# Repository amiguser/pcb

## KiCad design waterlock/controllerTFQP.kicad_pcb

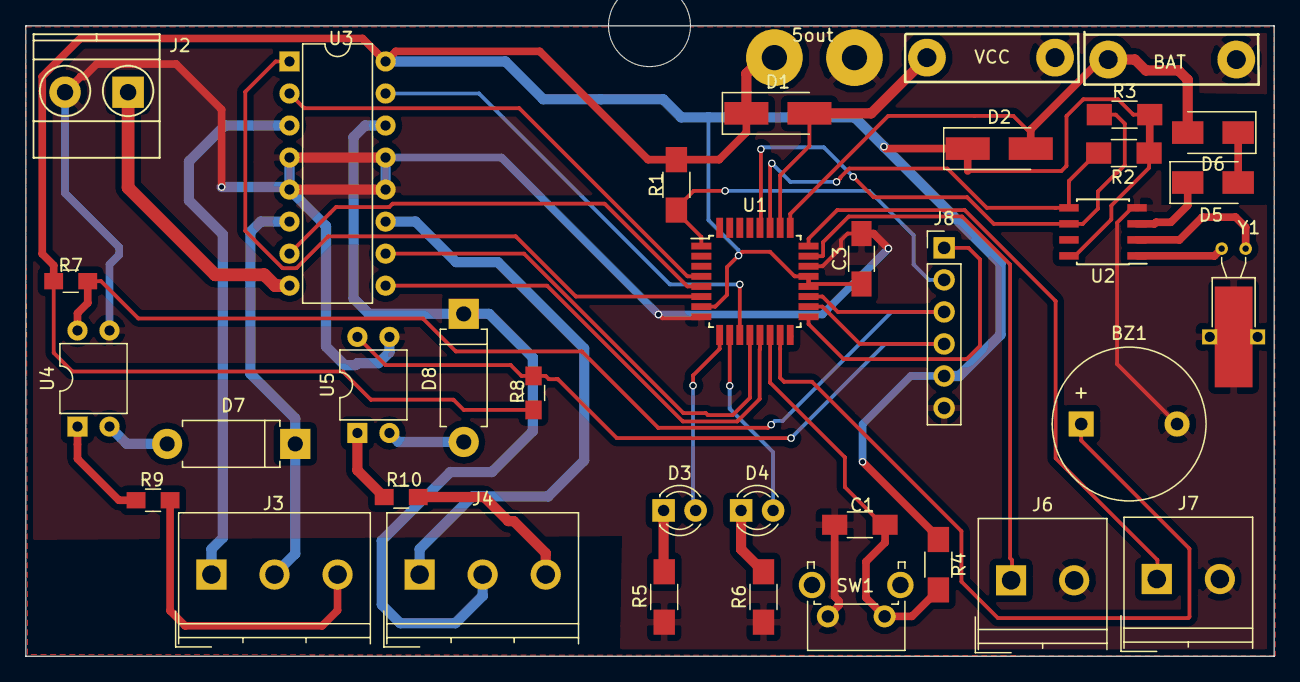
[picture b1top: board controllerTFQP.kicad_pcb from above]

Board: 2 copper layers, 99.0 x 50.0 mm, 37 parts (0 on the bottom side), 39 nets.

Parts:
5out: SolderWirePad_2x_2mmDrill
BAT: Battery; WireConnection_1.50mmDrill
BZ1: Buzzer; Buzzer_12x9.5RM7.6
C1, C3: 10m; C_1206_HandSoldering
D1: SS16; D_SMA_Handsoldering
D2: 1N; D_SMA_Handsoldering
D3: LowBatt; LED_D3.0mm
D4: Flooding; LED_D3.0mm
D5, D6: D_ALT; D_SMA
D7, D8: 1N5822; D_DO-15_P10.16mm_Horizontal
J2: v12; TerminalBlock_Pheonix_MKDS1.5-2pol
J3, J4: 300-031-7,5; TerminalBlock_Philmore_TB133_03x5mm_Straight
J6, J7: 301-021-12; TerminalBlock_Philmore_TB132_02x5mm_Straight
J8: Conn_01x06; Pin_Header_Straight_1x06_Pitch2.54mm
R1, R2, R3, R4, R5, R6: 10k; R_1206_HandSoldering
R7, R8: 10k; R_0805_HandSoldering
R9, R10: 1k; R_0805_HandSoldering
SW1: Tactile Angle; SW_Tactile_SPST_Angled_PTS645Vx39-2LFS
U1: ATMEGA8-16PU; TQFP-32_7x7mm_Pitch0.8mm
U2: DS1307+; SOIC-8_3.9x4.9mm_Pitch1.27mm
U3: L293D; DIP-16_W7.62mm
U4, U5: PC817; DIP-4_W7.62mm
VCC: v5; WireConnection_1.50mmDrill
Y1: 32768Hz; Crystal_C38-LF_d3.0mm_l8.0mm_Horizontal_1EP_style2

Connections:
+5V: 5out.1, C3.1, D1.1, D2.1, J8.5, R1.1, R2.2, R3.2, R4.1, R7.2, R8.2, U1.7, U1.20, U1.21, U2.8, U3.16
/Line1: J6.1, U1.23
/Line2: J7.1, U1.24
/MISO: J8.4, R8.1, U1.18, U5.4
/MOSI: J8.1, U1.17
/MotorsShield/m1black: D7.1, J3.2, U3.6
/MotorsShield/m1sensor: J3.3, R9.1
/MotorsShield/m2black: D8.1, J4.2, U3.14
/MotorsShield/m2sensor: J4.3, R10.1
/RESET: J8.2, R1.2, U1.1
/SCK: J8.3, R7.1, U1.19, U4.4
/SCL: R3.1, U1.28, U2.6
/SDA: R2.1, U1.27, U2.5
/btn_1: C1.2, R4.2, SW1.1, U1.14
/buzz: BZ1.1, U1.15
/en12: U1.6, U3.1
/en34: U1.13, U3.9
/led1: D3.2, U1.9
/led2: D4.2, U1.10
/m1a: U1.4, U3.2
/m2a: U1.5, U3.7
/m3a: U1.12, U3.10
/m4a: U1.11, U3.15
/pwr_c1: BAT.1, D2.2, D6.2, U1.25
/pwr_c2: D1.2, U1.26, VCC.1
GND: 5out.1, BAT.2, BZ1.2, C1.1, C3.2, J2.2, J6.2, J7.2, J8.6, R5.2, R6.2, SW1.2, U1.8, U1.22, U2.4, U3.4, U3.5, U3.12, U3.13, U4.3, U5.3, VCC.2, Y1.3
unnamed: D3.1, R5.1
unnamed: D4.1, R6.1
unnamed: D5.1, U2.3
unnamed: D5.2, D6.1
unnamed: D7.2, U4.2
unnamed: D8.2, U5.2
unnamed: J2.1, U3.8
unnamed: J3.1, U3.3
unnamed: J4.1, U3.11
unnamed: R9.2, U4.1
unnamed: R10.2, U5.1
unnamed: U2.1, Y1.1
unnamed: U2.2, Y1.2

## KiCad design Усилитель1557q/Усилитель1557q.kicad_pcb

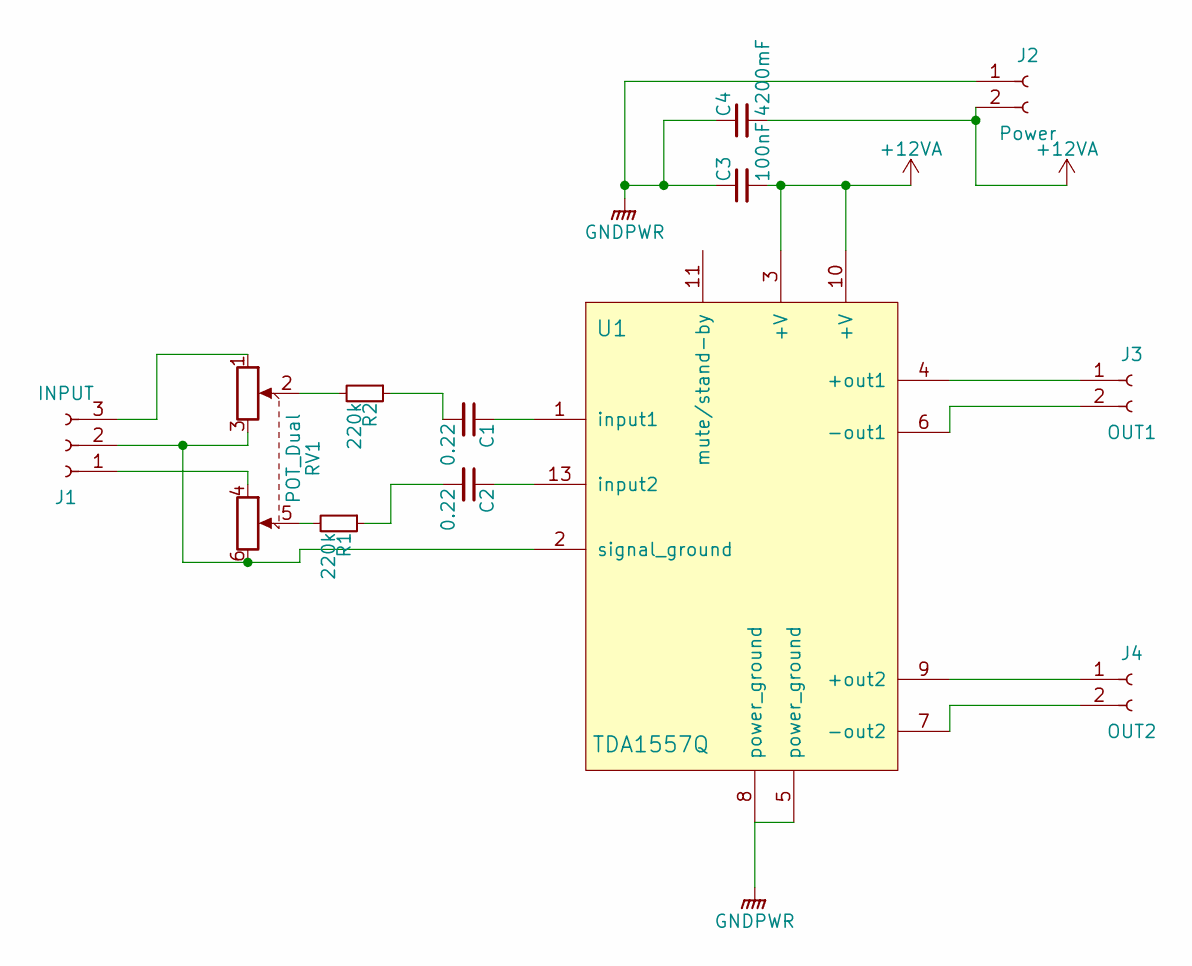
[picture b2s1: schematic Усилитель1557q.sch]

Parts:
C1, C2: 0.22; C_Disc_D11.0mm_W5.0mm_P7.50mm
C3: 100nF; C_Disc_D11.0mm_W5.0mm_P7.50mm
C4: 4200mF; CP_Radial_D13.0mm_P5.00mm
J1: INPUT; TerminalBlock_Pheonix_MKDS1.5-3pol
J2: Power; TerminalBlock_Pheonix_MKDS1.5-2pol
J3: OUT1; TerminalBlock_Pheonix_MKDS1.5-2pol
J4: OUT2; TerminalBlock_Pheonix_MKDS1.5-2pol
R1, R2: 220k; R_Axial_DIN0204_L3.6mm_D1.6mm_P7.62mm_Horizontal
RV1: POT_Dual; Potentiometer_Alps_RK163_Double_Vertical
U1: TDA1557Q; Multiwatt_15_Vertical

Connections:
+12VA: C3.2, C4.2, J2.2, U1.3 (+V), U1.10 (+V)
GNDPWR: C3.1, C4.1, J2.1, U1.5 (power_ground), U1.8 (power_ground)
unnamed: C1.1, U1.1 (input1)
unnamed: C1.2, R2.1
unnamed: C2.1, U1.13 (input2)
unnamed: C2.2, R1.1
unnamed: J1.1, RV1.4
unnamed: J1.2, RV1.3, RV1.6, U1.2 (signal_ground)
unnamed: J1.3, RV1.1
unnamed: J3.1, U1.4 (+out1)
unnamed: J3.2, U1.6 (-out1)
unnamed: J4.1, U1.9 (+out2)
unnamed: J4.2, U1.7 (-out2)
unnamed: R1.2, RV1.5
unnamed: R2.2, RV1.2

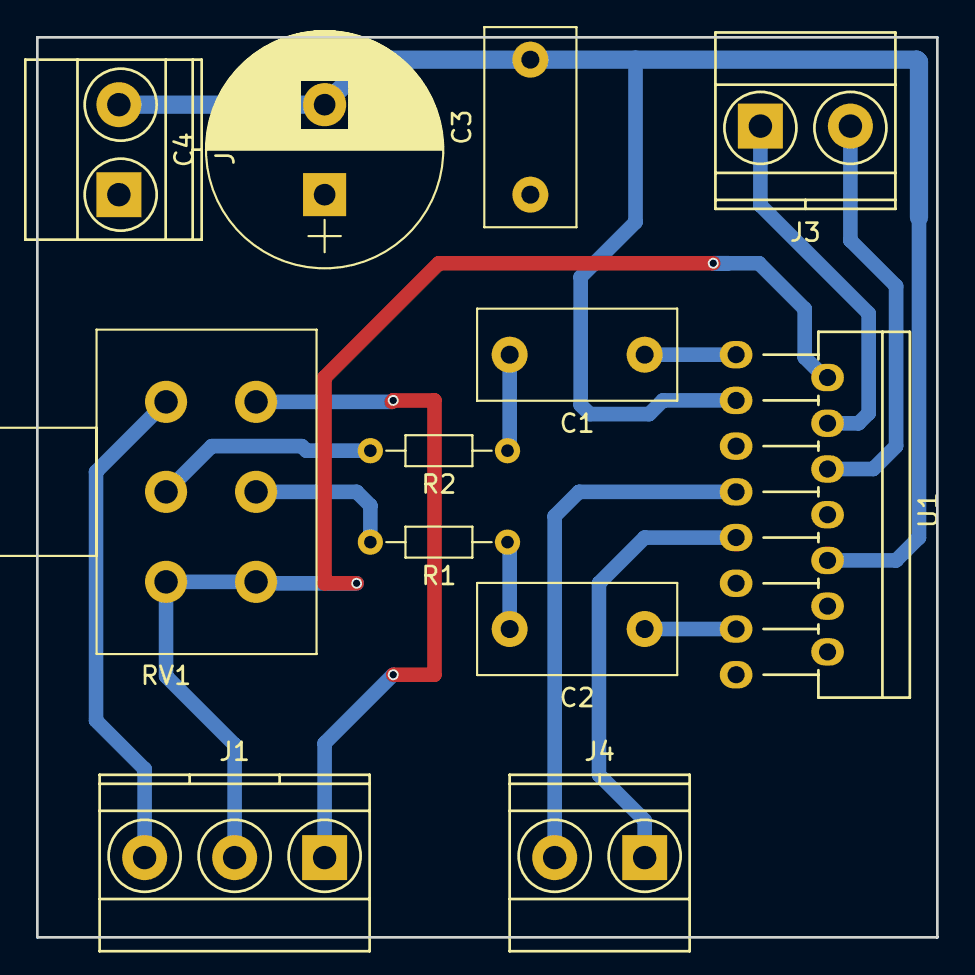
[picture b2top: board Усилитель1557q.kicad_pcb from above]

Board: 2 copper layers, 50.0 x 50.0 mm, 12 parts (0 on the bottom side), 15 nets.

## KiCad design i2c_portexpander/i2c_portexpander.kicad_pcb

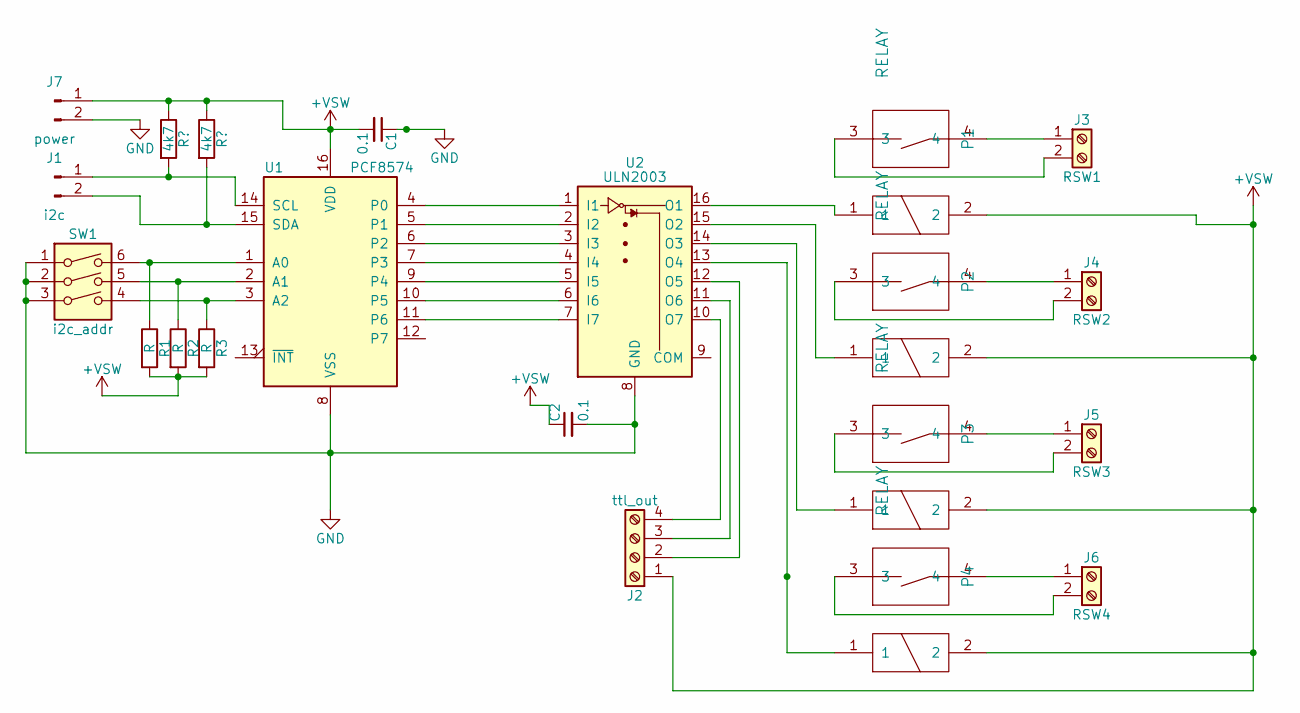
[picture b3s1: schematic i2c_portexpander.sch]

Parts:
C1, C2: 0.1; C_1206_HandSoldering
J1: i2c; Molex_KK-6410-02_02x2.54mm_Straight
J2: ttl_out; WAGO_734_4pin_Straight
J3: RSW1; TerminalBlock_Pheonix_MKDS1.5-2pol
J4: RSW2; TerminalBlock_Pheonix_MKDS1.5-2pol
J5: RSW3; TerminalBlock_Pheonix_MKDS1.5-2pol
J6: RSW4; TerminalBlock_Pheonix_MKDS1.5-2pol
J7: power; Molex_KK-6410-02_02x2.54mm_Straight
P1, P2, P3, P4: RELAY; Relay-841-1A
R1, R2, R3: R; R_0805_HandSoldering
SW1: i2c_addr; SW_DIP_x3_W8.61mm_Slide_LowProfile
U1: PCF8574; SOIC-16W_7.5x10.3mm_Pitch1.27mm
U2: ULN2003; SOIC-16W_5.3x10.2mm_Pitch1.27mm

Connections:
+VSW: C1.2, C2.1, J2.1, J7.1, P1.2, P2.2, P3.2, P4.2, R1.2, R2.2, R3.2, U1.16 (VDD); also elsewhere on the board
GND: C1.1, C2.2, J7.2, SW1.1, SW1.2, SW1.3, U1.8 (VSS), U2.8 (GND)
unnamed 2: J1.1, U1.14 (SCL); also elsewhere on the board
unnamed 3: J1.2, U1.15 (SDA); also elsewhere on the board
unnamed: J2.2, U2.12 (O5)
unnamed: J2.3, U2.11 (O6)
unnamed: J2.4, U2.10 (O7)
unnamed: J3.1, P1.4
unnamed: J3.2, P1.3
unnamed: J4.1, P2.4
unnamed: J4.2, P2.3
unnamed: J5.1, P3.4
unnamed: J5.2, P3.3
unnamed: J6.1, P4.4
unnamed: J6.2, P4.3
unnamed: P1.1, U2.16 (O1)
unnamed: P2.1, U2.15 (O2)
unnamed: P3.1, U2.14 (O3)
unnamed: P4.1, U2.13 (O4)
unnamed: R1.1, SW1.6, U1.1 (A0)
unnamed: R2.1, SW1.5, U1.2 (A1)
unnamed: R3.1, SW1.4, U1.3 (A2)
unnamed: U1.4 (P0), U2.1 (I1)
unnamed: U1.5 (P1), U2.2 (I2)
unnamed: U1.6 (P2), U2.3 (I3)
unnamed: U1.7 (P3), U2.4 (I4)
unnamed: U1.9 (P4), U2.5 (I5)
unnamed: U1.10 (P5), U2.6 (I6)
unnamed: U1.11 (P6), U2.7 (I7)

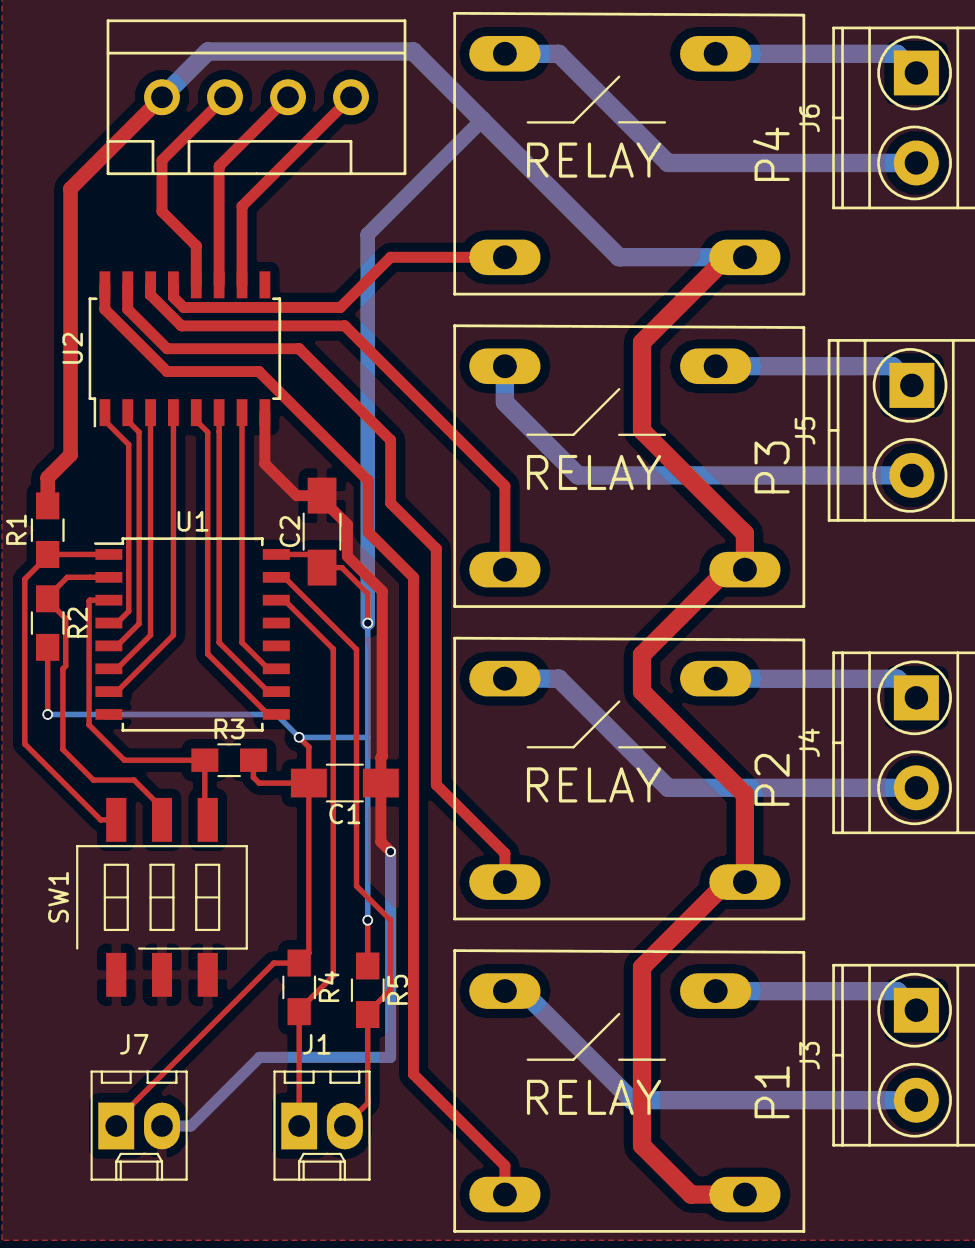
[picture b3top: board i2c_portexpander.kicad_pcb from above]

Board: 2 copper layers, 21 parts (0 on the bottom side), 29 nets.

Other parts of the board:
R4, R5: 4k7; R_0805_HandSoldering

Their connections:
+VSW: R4.1, R5.1; also elsewhere on the board
unnamed 2: R4.2; also elsewhere on the board
unnamed 3: R5.2; also elsewhere on the board

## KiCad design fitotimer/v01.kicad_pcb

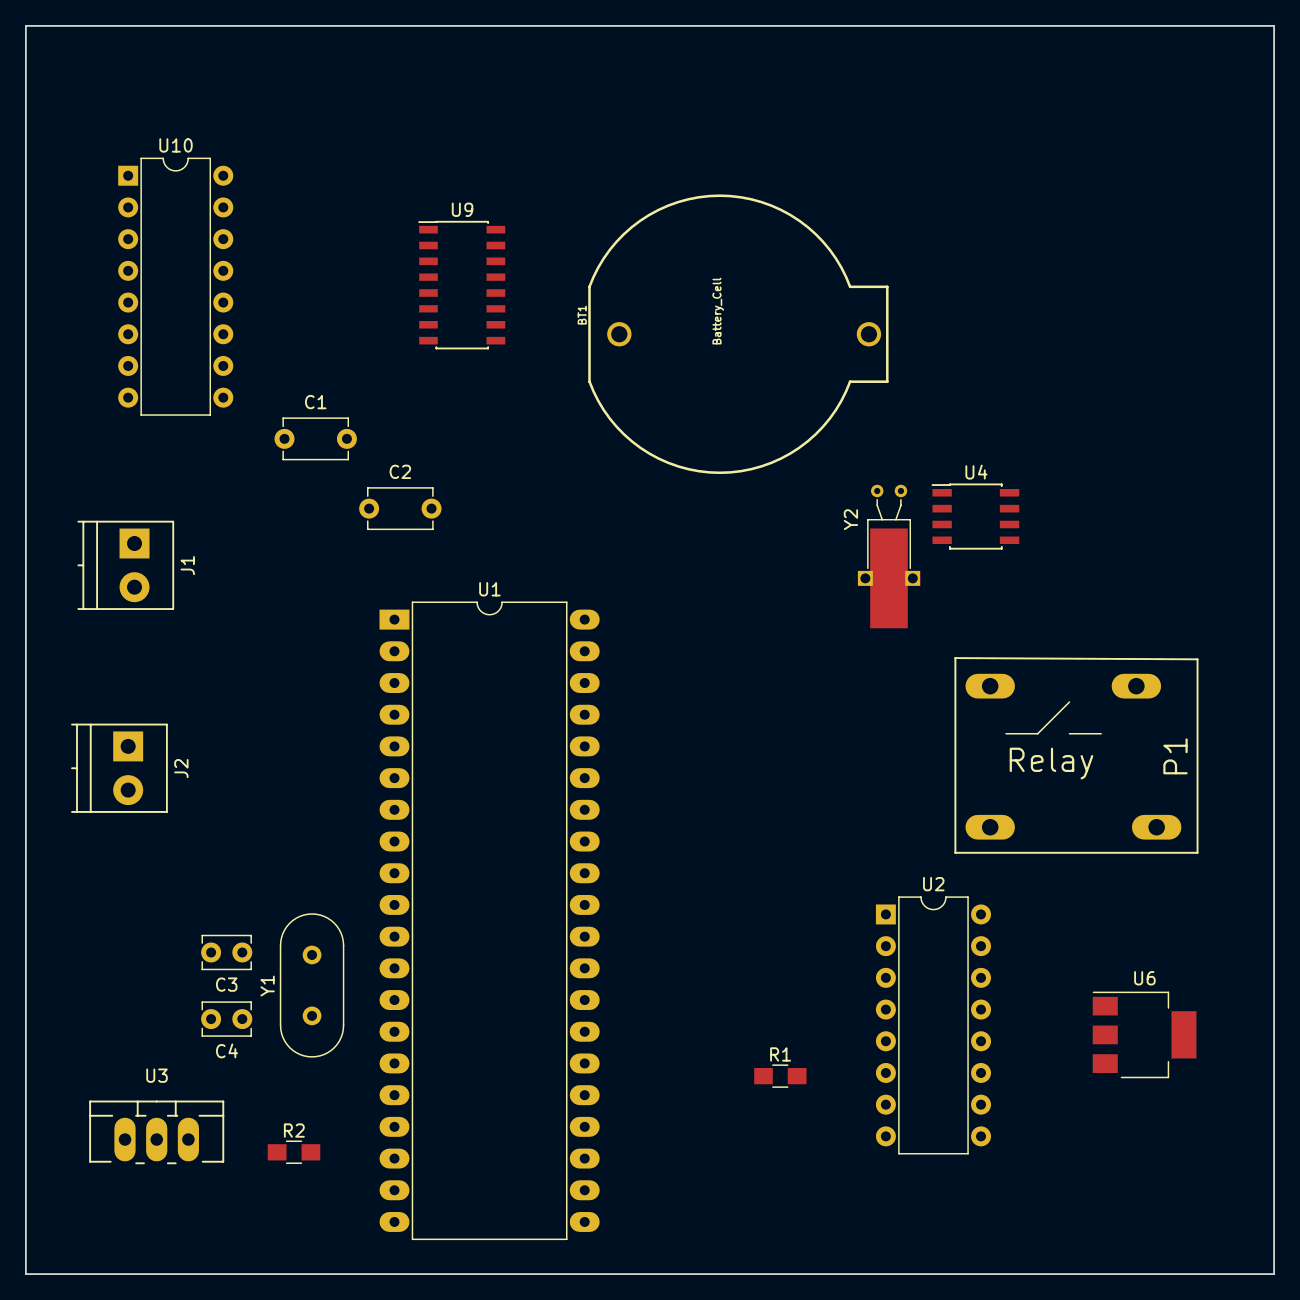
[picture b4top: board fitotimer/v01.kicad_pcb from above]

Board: 2 copper layers, 100.0 x 100.0 mm, 19 parts (0 on the bottom side), 17 nets, no tracks yet.

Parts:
BT1: Battery_Cell; BATTCOM_20MM_PTH
C1, C2: 0.1; C_Disc_D5.1mm_W3.2mm_P5.00mm
C3, C4: 0.1; C_Disc_D3.8mm_W2.6mm_P2.50mm
J1, J2: Screw_Terminal_01x02; TerminalBlock_Pheonix_PT-3.5mm_2pol
P1: Relay; Relay-841-1A
R1, R2: 4k7; R_0805_HandSoldering
U1: ATMEGA16-16PU; DIP-40_W15.24mm_LongPads
U2: L293D; DIP-16_W7.62mm
U3: L7805; TO-220_Neutral123_Vertical_LargePads
U4: DS1307+; SOIC-8_3.9x4.9mm_Pitch1.27mm
U6: LM1117-3.3; SOT-223
U9: PCF8574; SOIC-16_3.9x9.9mm_Pitch1.27mm
U10: ULN2003; DIP-16_W7.62mm
Y1: 8Mhz; Crystal_HC49-4H_Vertical
Y2: 32768; Crystal_C38-LF_d3.0mm_l8.0mm_Horizontal_1EP_style2

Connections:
+5VA: C1.2, C2.1, R1.1, R2.1, U1.10, U1.30, U3.3, U4.8, U6.3, U9.16
GND: BT1.2, C1.1, C2.2, U1.11, U1.31, U3.2, U4.4, U6.1, U9.8, U10.8
unnamed: BT1.1, U4.3
unnamed: C3.1, U1.12, Y1.2
unnamed: C3.2, C4.2
unnamed: C4.1, U1.13, Y1.1
unnamed: U4.1, Y2.1
unnamed: U4.2, Y2.2
unnamed: U9.4, U10.1
unnamed: U9.5, U10.2
unnamed: U9.6, U10.3
unnamed: U9.7, U10.4
unnamed: U9.9, U10.5
unnamed: U9.10, U10.6
unnamed: U9.11, U10.7
SCL: R2.2, U1.22, U4.6, U9.14
SDA: R1.2, U1.23, U4.5, U9.15

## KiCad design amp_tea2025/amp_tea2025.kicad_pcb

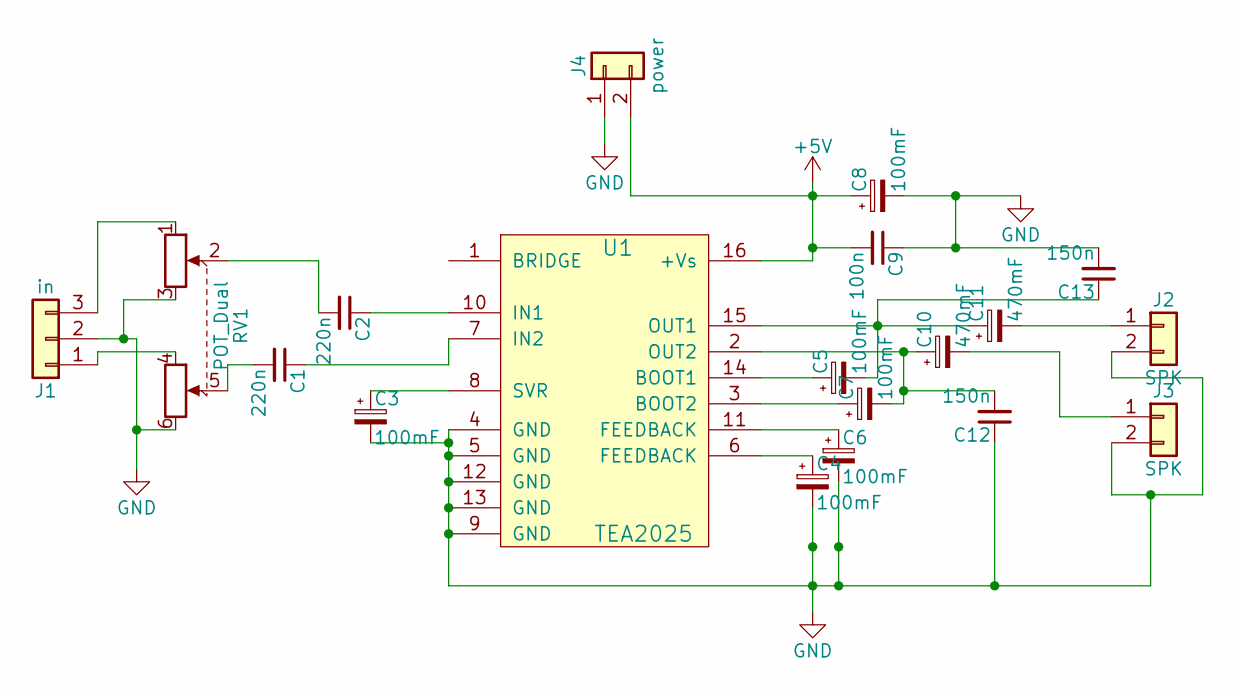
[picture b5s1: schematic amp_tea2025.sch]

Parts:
C1, C2: 220n; C_Disc_D9.0mm_W5.0mm_P10.00mm
C3, C4, C5, C6, C7, C8: 100mF; CP_Radial_D8.0mm_P5.00mm
C9: 100n; C_Disc_D9.0mm_W5.0mm_P10.00mm
C10, C11: 470mF; CP_Radial_D10.0mm_P5.00mm
C12, C13: 150n; C_Disc_D9.0mm_W5.0mm_P10.00mm
J1: in; WAGO_734_3pin_Straight
J2, J3: SPK; WAGO_734_2pin_Straight_RuggedPads
J4: power; WAGO_734_2pin_Straight_RuggedPads
RV1: POT_Dual; Potentiometer_Alps_RK163_Double_Vertical
U1: TEA2025; DIP-16_W7.62mm

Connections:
+5V: C8.1, C9.2, J4.2, U1.16 (+Vs)
GND: C3.2, C4.2, C6.2, C8.2, C9.1, C12.1, C13.2, J1.2, J2.2, J3.2, J4.1, RV1.3, RV1.6, U1.4 (GND), U1.5 (GND), U1.9 (GND), U1.12 (GND), U1.13 (GND)
unnamed: C1.1, U1.7 (IN2)
unnamed: C1.2, RV1.5
unnamed: C2.1, U1.10 (IN1)
unnamed: C2.2, RV1.2
unnamed: C3.1, U1.8 (SVR)
unnamed: C4.1, U1.6 (FEEDBACK)
unnamed: C5.1, U1.14 (BOOT1)
unnamed: C6.1, U1.11 (FEEDBACK)
unnamed: C7.1, U1.3 (BOOT2)
unnamed: C7.2, C10.1, C12.2, U1.2 (OUT2)
unnamed: C10.2, J3.1
unnamed: C5.2, C11.1, C13.1, U1.15 (OUT1)
unnamed: C11.2, J2.1
unnamed: J1.1, RV1.4
unnamed: J1.3, RV1.1

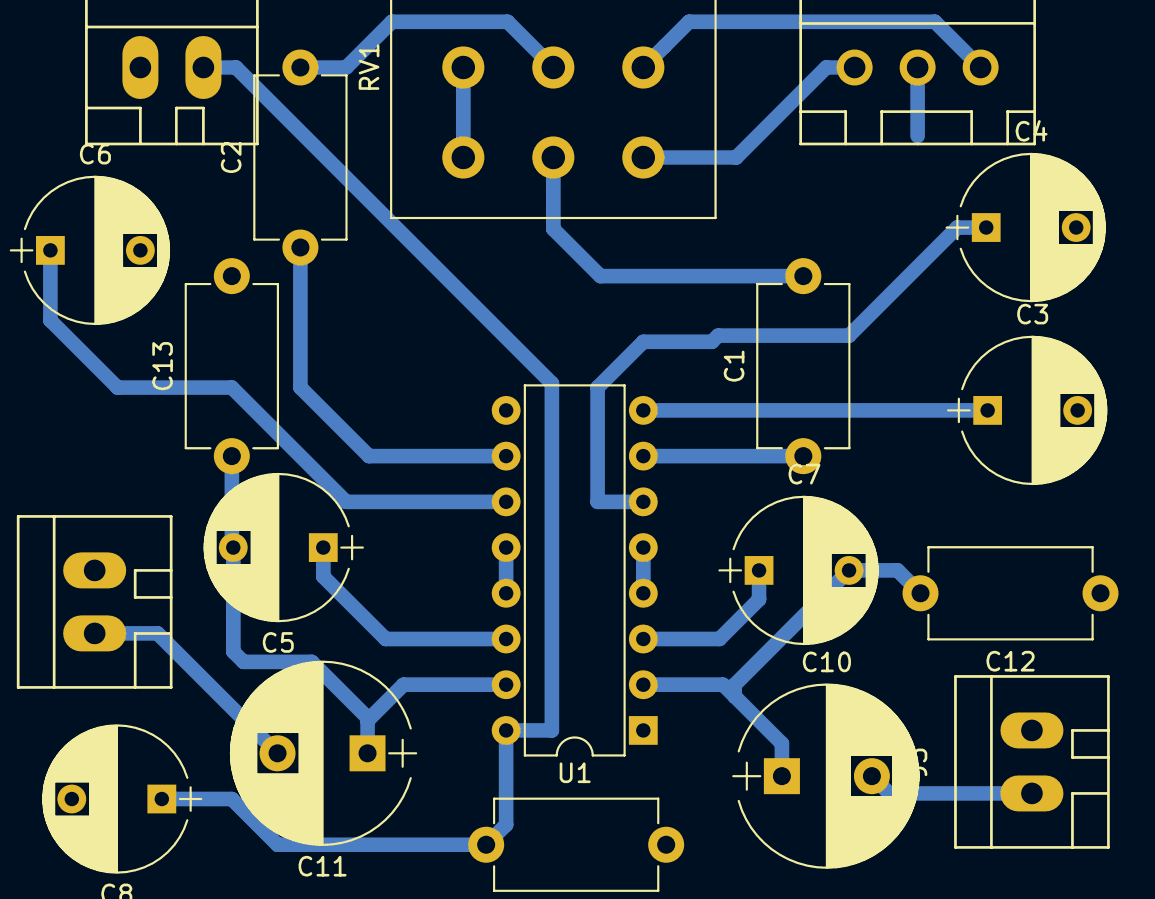
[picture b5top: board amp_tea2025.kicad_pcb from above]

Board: 2 copper layers, 19 parts (0 on the bottom side), 17 nets.

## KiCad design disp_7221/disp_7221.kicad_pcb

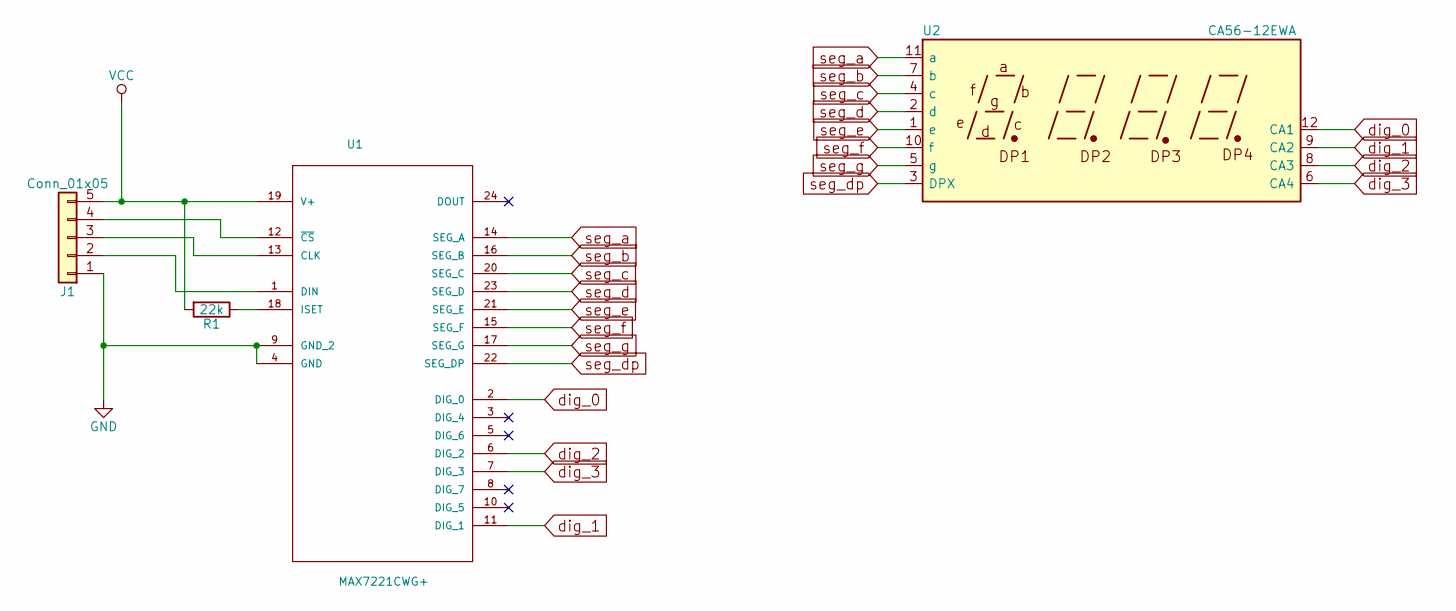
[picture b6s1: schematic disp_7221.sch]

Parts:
J1: Conn_01x05; Molex_KK-6410-05_05x2.54mm_Straight
R1: 22k; R_0805_HandSoldering
U1: MAX7221CWG+; SOIC-24_7.5x15.4mm_Pitch1.27mm
U2: CA56-12EWA; Cx56-12

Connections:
GND: J1.1, U1.4 (GND), U1.9 (GND_2)
unnamed: J1.2, U1.1 (DIN)
unnamed: J1.3, U1.13 (CLK)
unnamed: J1.4, U1.12 (~CS)
unnamed: R1.1, U1.18 (ISET)
VCC: J1.5, R1.2, U1.19 (V+)
dig_0: U1.2 (DIG_0), U2.12 (CA1)
dig_1: U1.11 (DIG_1), U2.9 (CA2)
dig_2: U1.6 (DIG_2), U2.8 (CA3)
dig_3: U1.7 (DIG_3), U2.6 (CA4)
seg_a: U1.14 (SEG_A), U2.11 (a)
seg_b: U1.16 (SEG_B), U2.7 (b)
seg_c: U1.20 (SEG_C), U2.4 (c)
seg_d: U1.23 (SEG_D), U2.2 (d)
seg_dp: U1.22 (SEG_DP), U2.3 (DPX)
seg_e: U1.21 (SEG_E), U2.1 (e)
seg_f: U1.15 (SEG_F), U2.10 (f)
seg_g: U1.17 (SEG_G), U2.5 (g)

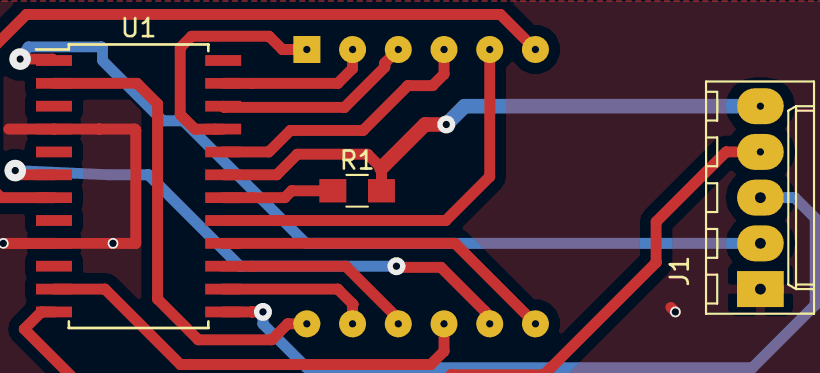
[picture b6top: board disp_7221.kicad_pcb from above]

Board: 2 copper layers, 4 parts (1 on the bottom side), 18 nets.

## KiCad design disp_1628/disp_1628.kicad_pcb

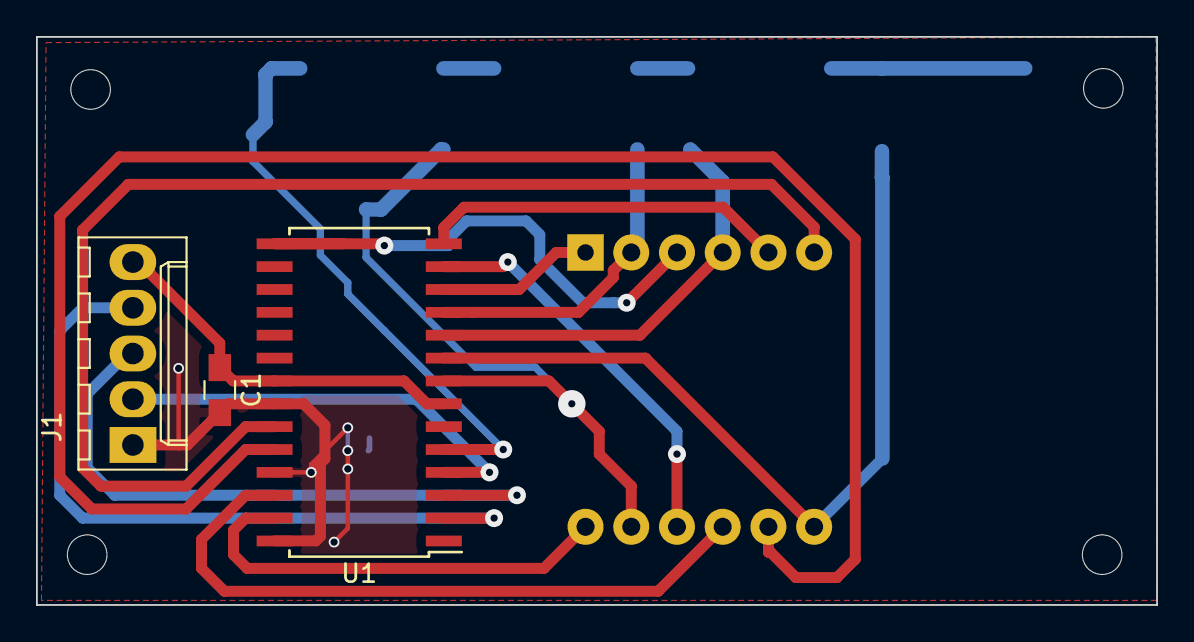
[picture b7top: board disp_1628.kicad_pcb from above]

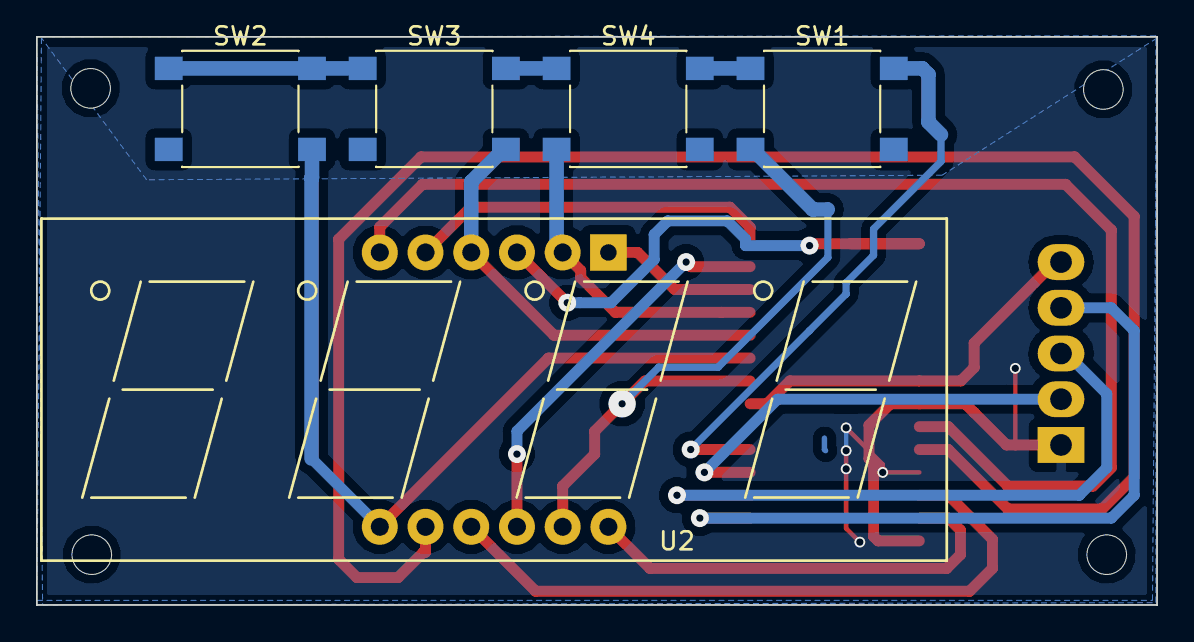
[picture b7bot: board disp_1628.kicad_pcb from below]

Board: 2 copper layers, 62.2 x 31.6 mm, 8 parts (5 on the bottom side), 18 nets.

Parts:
C1: 0.1; C_0805_HandSoldering
J1: Conn_01x05; Molex_KK-6410-05_05x2.54mm_Straight
SW1, SW2, SW3, SW4: SW_Push; SW_SPST_PTS645
U1: TM1628; SOIC-28W_7.5x17.9mm_Pitch1.27mm
U2: CA56-12EWA; Cx56-12

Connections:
GND: C1.2, J1.1, U1.22, U1.25, U1.28
K1: SW1.1, SW2.1, SW3.1, SW4.1, U1.5
unnamed: J1.2, U1.4
unnamed: J1.3, U1.3
unnamed: J1.4, U1.2
VCC: C1.1, J1.5, U1.7, U1.21
dig_0: U1.27, U2.12
dig_1: U1.26, U2.9
dig_2: U1.24, U2.8
dig_3: U1.23, U2.6
seg_a: SW1.2, U1.8, U2.11
seg_b: SW2.2, U1.9, U2.7
seg_c: SW3.2, U1.10, U2.4
seg_d: SW4.2, U1.11, U2.2
seg_dp: U1.15, U2.3
seg_e: U1.12, U2.1
seg_f: U1.13, U2.10
seg_g: U1.14, U2.5

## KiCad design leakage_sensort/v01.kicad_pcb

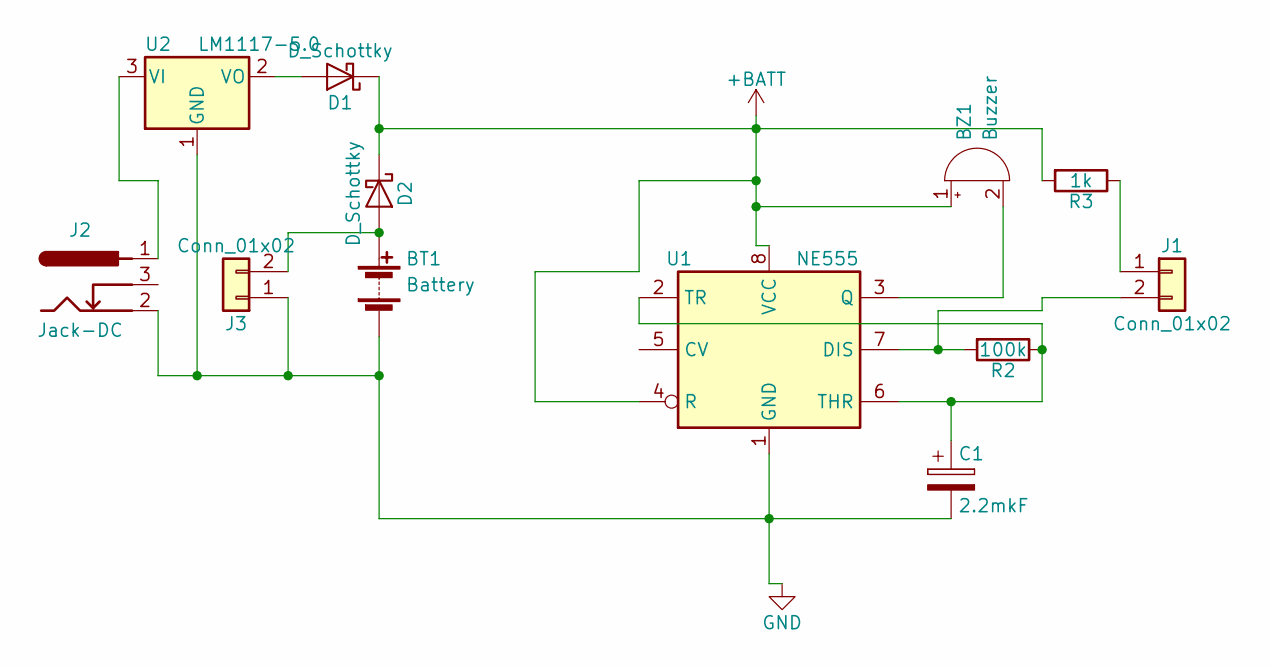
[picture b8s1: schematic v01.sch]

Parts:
BT1: Battery; Keystone_2479_3xAAA
BZ1: Buzzer; Buzzer_12x9.5RM7.6
C1: 2.2mkF; CP_Radial_D5.0mm_P2.50mm
D1, D2: D_Schottky; D_SMB_Handsoldering
J1, J3: Conn_01x02; Pin_Header_Straight_1x02_Pitch2.54mm
J2: Jack-DC; JACK_ALIM
R2: 100k; R_1206_HandSoldering
R3: 1k; R_1206_HandSoldering
U1: NE555; SOIC-8_3.9x4.9mm_Pitch1.27mm
U2: LM1117-5.0; SOT-223

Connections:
+BATT: BZ1.1 (-), D1.1 (K), D2.1 (K), R3.2, U1.4 (R), U1.8 (VCC)
GND: BT1.2 (-), C1.2, J2.2, J3.1, U1.1 (GND), U2.1 (GND)
unnamed: BT1.1 (+), D2.2 (A), J3.2
unnamed: BZ1.2 (+), U1.3 (Q)
unnamed: C1.1, R2.1, U1.2 (TR), U1.6 (THR)
unnamed: D1.2 (A), U2.2 (VO)
unnamed: J1.1, R3.1
unnamed: J1.2, R2.2, U1.7 (DIS)
unnamed: J2.1, U2.3 (VI)

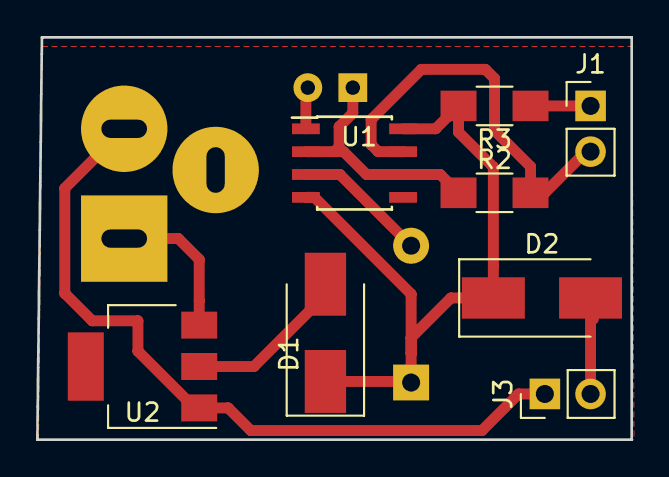
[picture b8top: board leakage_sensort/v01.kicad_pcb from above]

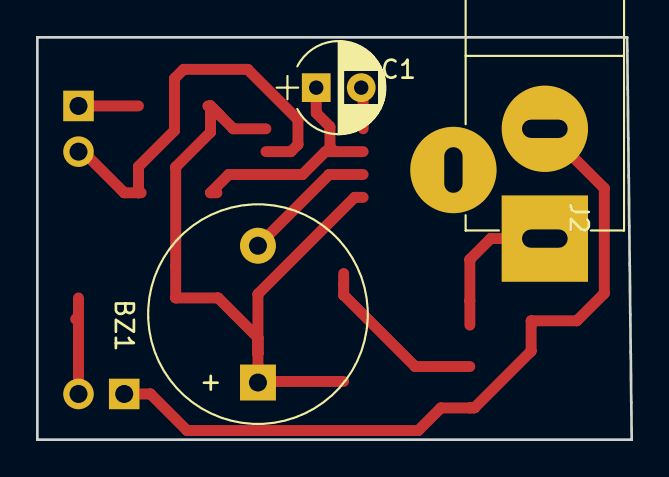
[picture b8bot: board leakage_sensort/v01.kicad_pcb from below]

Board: 2 copper layers, 33.0 x 22.4 mm, 11 parts (3 on the bottom side), 9 nets.

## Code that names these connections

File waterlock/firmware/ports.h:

/*
 * ports.h
 *
 *  Created on: Sep 6, 2018
 *      Author: mih
 */

#ifndef PORTS_H_
#define PORTS_H_

//PORTB
#define LED1 PB6 //Red
#define LED2 PB7 //Green
#define BTN1 PB0
#define BUZZ PB1

//PORTC
#define LINE1 PC0
#define LINE2 PC1
#define POWER1 PC2 //Control 12V battery power
#define POWER2 PC3 //Control 12V AC/DC power

//PORTD
#define M1A PD2
#define M2A PD3
#define EN12 PD4
#define M3A PD6
#define M4A PD5
#define EN34 PD7

#define TIME2TURN 15 //seconds
#define STATUS_LEAKAGE 1
#define STATUS_DUTY 2
#define STATUS_TEST 3
#define STATUS_AC_LOW 4
#define STATUS_BAT_LOW 5

#define KEYS_NOKEY 0
#define KEYS_1PRESS 1
#define KEYS_5PRESS 5
#define KEYS_LONGPRESS 10


#endif /* PORTS_H_ */

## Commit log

2018-07-30 initial
2018-08-01 tea2025
2018-08-15 1557q-improved
2018-08-31 waterlock init
2018-09-07 firmware start
2018-09-18 teplica
2018-09-28 prot
2018-10-11 up01
2018-11-01 fware
2018-11-07 acquire
2018-11-08 keys
2018-11-08 set time delays
2018-11-13 full cycle
2018-11-20 newpcb
2018-11-20 sensor
2018-11-30 tqfp
2018-12-02 ddpcb+
2018-12-05 new wave
2018-12-20 pcb-prod
2018-12-23 input 5v
2018-12-29 prod
2019-01-23 chicken
2019-01-24 fixing point
2019-03-01 encoder
2019-04-30 weather
